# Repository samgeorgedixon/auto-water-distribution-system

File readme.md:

# Regulated Irrigation System (RIS)

**Modular, reliable and fine controlled irrigation for home to industrial greenhouses or farms, while adapting to varied temperatures and seasons to conserve water and ensure plant health.**

## Overview

Regulated Irrigation System (RIS) is modular irrigation system designed for everything from a small greenhouse to industrial farm setups. It gives you detailed control over watering routines and is able to adapt its watering output based on temperature and season. It does this while running reliably all year round unattended while conserving water.

From a phone / desktop browser you can schedule routines to water certain sets of plants at different times or intervals for durations based of current environment conditions.

#### Key Features

1. Water Plants (Water Conservation).
2. Any Environment and Scale (Greenhouse / Farm).
3. Reliable (Works for Months / Years).
4. Sustainable (Self Sufficient: Solar / Rain).
5. Relatively Affordable (< ~£100).

#### Modules

This design is made up of multiple modules which allow it to scale to any scenario with them able to sit flat on a table or be easily mounted onto a wall with keyholes.

- Command Module: Central, controlling all other modules based on the routines you have set.
- Switch modules: Add as many as needed where they interface with command to turn on certain ones of its 6 ports to power your water pumps or valves when needed.
- Valves / Pumps: Allow water to be pumped to specific sets of plants for different durations giving you full control.

#### Power

All operates off 1 battery that is charged continuously with a solar panel to ensure it can run for years in remote locations like an allotment or field.

You can then choose to power the pumps and valves by another source like mains or an external battery pack if they require more power in industrial environments.

## Small Greenhouse Scenario

To take advantage of it in this scenario you can have both sides of the greenhouse on different valves because they may get a different amount of sunlight or have different varieties of plant so one side needs more water than the other.

1. Then you can have a pump that is operated with each valve at a time taking water out of a water tank and distributing it but also have another that fills the tank every couple weeks with more water from a water butt.
2. Due to only giving the plants the water they need they will have increased yields, and it will conserve water which is important when using a water butt as when there is little rainfall it will still have leftover water.
3. As well as this due to water duration being done based of temperature, across the year plants will get more water in the summer when they need it more and little to none in the winter when they don’t need it.

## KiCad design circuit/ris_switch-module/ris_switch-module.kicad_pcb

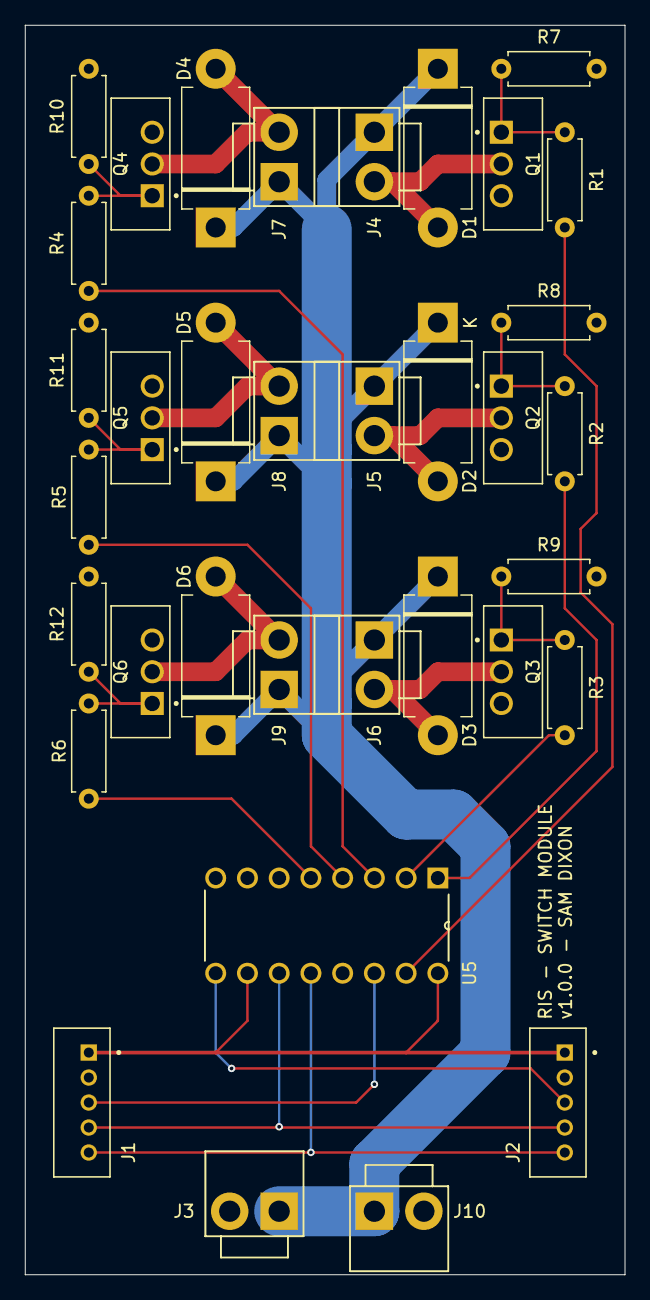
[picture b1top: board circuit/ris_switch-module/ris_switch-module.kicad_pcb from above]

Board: 2 copper layers, 48.0 x 100.0 mm, 35 parts (0 on the bottom side), 25 nets.

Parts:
D1, D2, D3, D4, D5, D6: D; D_DO-201AD_P12.70mm_Horizontal
J1, J2: JST-PH-5P-M; JST_B5B-PH-K-S
J3, J10: JST-B2PS-VH-M; B2P-VH
J4, J5, J6, J7, J8, J9: JST-PH-2P-M; B2P-VH
Q1, Q2, Q3, Q4, Q5, Q6: IRLZ44N; TO254P1054X469X1930-3
R1, R2, R3, R4, R5, R6: R-220; R_Axial_DIN0207_L6.3mm_D2.5mm_P7.62mm_Horizontal
R7, R8, R9, R10, R11, R12: R-10k; R_Axial_DIN0207_L6.3mm_D2.5mm_P7.62mm_Horizontal
U5: 74HC595N_112; DIP254P762X420-16

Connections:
GND: J1.2, J2.2, J3.2, J10.2, Q1.3, Q2.3, Q3.3, Q4.3, Q5.3, Q6.3, R7.1, R8.1, R9.1, R10.1, R11.1, R12.1, U5.8 (GND), U5.13 (~OE)
unnamed: D1.2 (A), J4.2, Q1.2
unnamed: D1.1 (K), D2.1 (K), D3.1 (K), D4.1 (K), D5.1 (K), D6.1 (K), J3.1, J4.1, J5.1, J6.1, J7.1, J8.1, J9.1, J10.1
unnamed: D2.2 (A), J5.2, Q2.2
unnamed: D3.2 (A), J6.2, Q3.2
unnamed: D4.2 (A), J7.2, Q4.2
unnamed: D5.2 (A), J8.2, Q5.2
unnamed: D6.2 (A), J9.2, Q6.2
unnamed: J1.1, J2.1, U5.10 (~MR), U5.16 (VCC)
unnamed: J1.3, U5.14 (DS)
unnamed: J1.4, J2.4, U5.11 (SH_CP)
unnamed: J1.5, J2.5, U5.12 (ST_CP)
unnamed: J2.3, U5.9 (Q7_2)
unnamed: Q1.1, R1.2, R7.2
unnamed: Q2.1, R2.2, R8.2
unnamed: Q3.1, R3.2, R9.2
unnamed: Q4.1, R4.2, R10.2
unnamed: Q5.1, R5.2, R11.2
unnamed: Q6.1, R6.2, R12.2
unnamed: R1.1, U5.15 (Q0)
unnamed: R2.1, U5.1 (Q1)
unnamed: R3.1, U5.2 (Q2)
unnamed: R4.1, U5.3 (Q3)
unnamed: R5.1, U5.4 (Q4)
unnamed: R6.1, U5.5 (Q5)

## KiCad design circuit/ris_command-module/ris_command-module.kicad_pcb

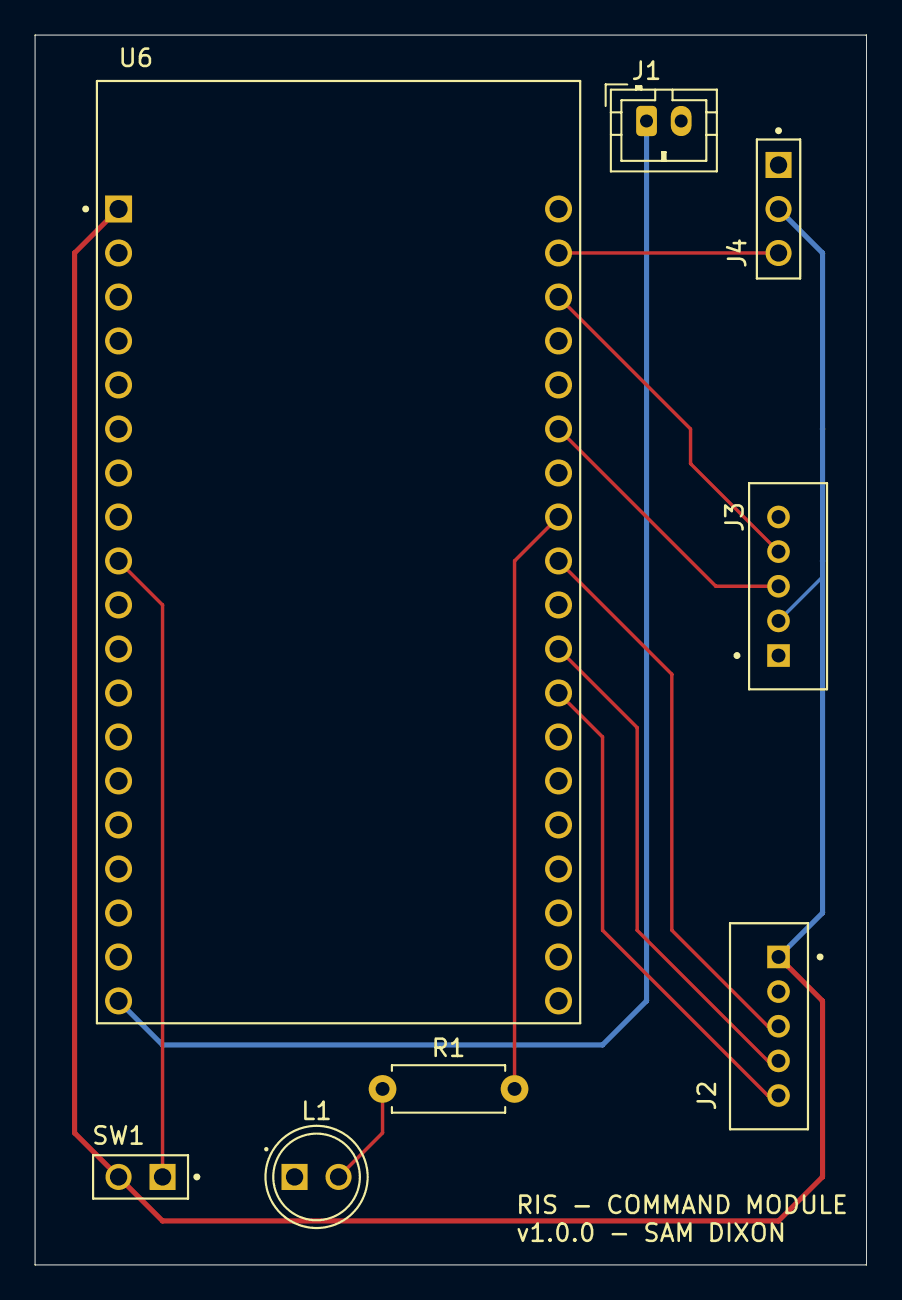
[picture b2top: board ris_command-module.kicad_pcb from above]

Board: 2 copper layers, 48.0 x 71.0 mm, 8 parts (0 on the bottom side), 12 nets.

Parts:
J1: JST-PH-2P-M_5V; JST_PH_B2B-PH-K_1x02_P2.00mm_Vertical
J2: JST-PH-5P-M; JST_B5B-PH-K-S
J3: JST-PH-5P-M_ZS042; JST_B5B-PH-K-S
J4: Header-3P-F_DHT22; HARWIN_M20-7820346
L1: WP7113ID; LED_WP7113ID
R1: R-220; R_Axial_DIN0207_L6.3mm_D2.5mm_P7.62mm_Horizontal
SW1: SW_DIP_x01; HARWIN_M20-7820242
U6: ESP32-DEVKITC-32D; MODULE_ESP32-DEVKITC-32D

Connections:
+3.3V: J2.1, J3.2, J4.2, SW1.2, U6.J2-1 (3V3)
+5V: J1.1, U6.J2-19 (EXT_5V)
GND: J1.2, J2.2, J3.1, J4.1, L1.C, U6.J3-1 (GND3)
unnamed: J2.3, U6.J3-9 (IO18)
unnamed: J2.4, U6.J3-11 (IO17)
unnamed: J2.5, U6.J3-12 (IO16)
unnamed: J3.3, U6.J3-6 (IO21)
unnamed: J3.4, U6.J3-3 (IO22)
unnamed: J4.3, U6.J3-2 (IO23)
unnamed: L1.A, R1.1
unnamed: R1.2, U6.J3-8 (IO19)
unnamed: SW1.1, U6.J2-9 (IO25)

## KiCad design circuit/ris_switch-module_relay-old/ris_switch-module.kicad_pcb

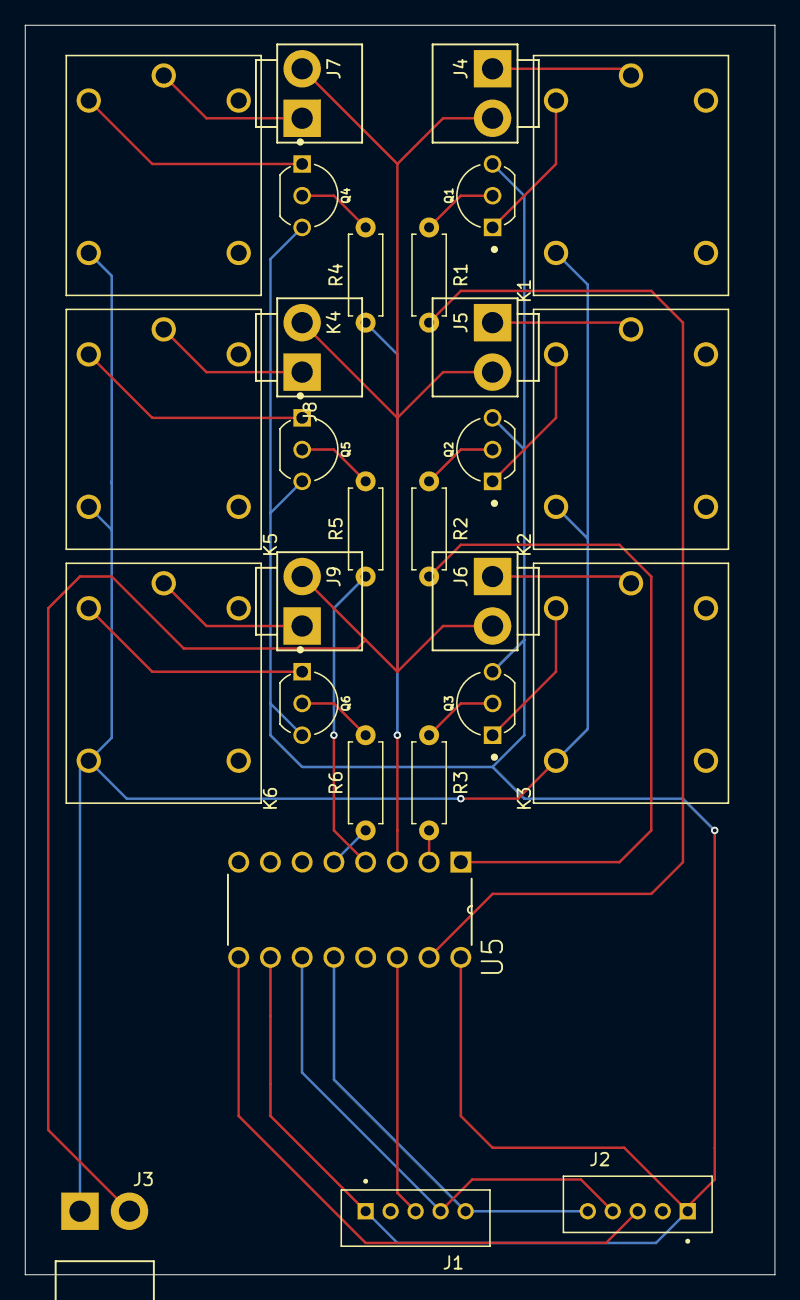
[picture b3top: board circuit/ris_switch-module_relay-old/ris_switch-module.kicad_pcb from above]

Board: 2 copper layers, 60.0 x 100.0 mm, 28 parts (0 on the bottom side), 32 nets.

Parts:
J1, J2: JST-PH-5P-M; JST_B5B-PH-K-S
J3: JST-B2PS-VH-M; B2PS-VH
J4, J5, J6, J7, J8, J9: JST-PH-2P-M; B2P-VH
K1, K2, K3, K4, K5, K6: SRD-03VDC-SL-C; RELAY_SRD-03VDC-SL-C
Q1, Q2, Q3, Q4, Q5, Q6: BC337-40; TO92254P520H877-3
R1, R2, R3, R4, R5, R6: R-470; R_Axial_DIN0207_L6.3mm_D2.5mm_P7.62mm_Horizontal
U5: 74HC595N_112; DIP254P762X420-16

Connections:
unnamed: J1.1, J2.1, Q1.3 (C), Q2.3 (C), Q3.3 (C), Q4.3 (C), Q5.3 (C), Q6.3 (C), U5.10 (~MR), U5.16 (VCC)
unnamed: J1.2, J2.2, K1.COIL1, K2.COIL1, K3.COIL1, K4.COIL1, K5.COIL1, K6.COIL1, U5.8 (GND), U5.13 (~OE)
unnamed: J1.3, U5.14 (DS)
unnamed: J1.4, J2.4, U5.11 (SH_CP)
unnamed: J1.5, J2.5, U5.12 (ST_CP)
unnamed: J2.3, U5.9 (Q7_2)
unnamed: J3.1, K1.NO, K2.NO, K3.NO, K4.NO, K5.NO, K6.NO
unnamed: J3.2, J4.2, J5.2, J6.2, J7.2, J8.2, J9.2
unnamed: J4.1, K1.COM
unnamed: J5.1, K2.COM
unnamed: J6.1, K3.COM
unnamed: J7.1, K4.COM
unnamed: J8.1, K5.COM
unnamed: J9.1, K6.COM
unnamed: Q1.2 (B), R1.2
unnamed: K1.COIL2, Q1.1 (E)
unnamed: Q2.2 (B), R2.2
unnamed: K2.COIL2, Q2.1 (E)
unnamed: Q3.2 (B), R3.2
unnamed: K3.COIL2, Q3.1 (E)
unnamed: Q4.2 (B), R4.2
unnamed: K4.COIL2, Q4.1 (E)
unnamed: Q5.2 (B), R5.2
unnamed: K5.COIL2, Q5.1 (E)
unnamed: Q6.2 (B), R6.2
unnamed: K6.COIL2, Q6.1 (E)
unnamed: R1.1, U5.15 (Q0)
unnamed: R2.1, U5.1 (Q1)
unnamed: R3.1, U5.2 (Q2)
unnamed: R4.1, U5.3 (Q3)
unnamed: R5.1, U5.4 (Q4)
unnamed: R6.1, U5.5 (Q5)

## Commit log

2025-07-30 Added Git
2025-07-31 Added Flow System Diagram
2025-07-31 Added Circuit and Model CAD
2025-08-04 Added Basic Model Blocks
2025-09-07 Added Component Orders Spreadsheet
2025-09-07 Added Command and Switch Modules
2025-11-08 Updated README with Plan & Reorganised Folders
2025-11-08 Added Command Module Circuit
2025-11-08 Updated Circuit
2025-11-09 Updated Model
2025-11-09 Added Switches and LED to Circuit
2025-11-12 Updated Component Orders with Exact Electronic Components
2025-11-15 Updated Model with Perfboard
2025-11-18 Added Program with Components
2025-11-23 Updated Program with Network and Flow
2025-11-23 Changed Name to Regulated Irrigation System (RIS)
2025-12-03 Updated Program with Routines & Time & Saving
2025-12-14 Added Command & Switch PCBs
2025-12-19 Updated Program with Pump / Valve Port Selections
2025-12-20 Updated Program with HTML Refactor + Pin Skips
2025-12-22 Updated Program with Current / Power Limits
2025-12-27 Fitted Electronic Components into Model
2025-12-30 Updated Program with Input Limits & Time & Power Saving
2025-12-31 Updated Circuit with Side Outputs & Mosfets
2026-01-02 Updated Model with Connectors / Slots
2026-01-02 Updated Model with Time & Temperature Enclosure Parts
2026-01-03 Updated Model with Keyhole Mounting to Slot Module
2026-01-03 Updated Model with Solar Charger Connector
2026-01-03 Updated Model with Valve Module
2026-01-03 Added Design & Presentation Documents
2026-01-04 Fixed Circuit by DRC
2026-01-04 Updated Component Orders
2026-01-17 Exported Circuits to Gerber files
2026-01-17 Updated Order List
2026-01-18 Updated Order List with Separated Components
2026-02-13 Updated Model Tolerances
2026-02-22 Fixed Model Tolerances
2026-02-22 Fixed Program with Routine Starting & Switch Logic
2026-03-01 Fixed Program with Routines Timing
2026-03-12 Refactored Project Structure
2026-03-14 Updated License with Hardware & Software Licenses
2026-03-14 Removed .code-workspace
2026-03-14 Release: v0.1.0
    commit 395d54a6aa0ec5e2283e6a57e1ed26b426e7688f
    Author: Sam Dixon <samgeorgedixon@gmail.com>
    Date: Sat Mar 14 11:14:19 2026 +0000
    Removed .code-workspace
    commit e84a8b03ed0aea64cf1571eb71c593b8f5143728
    Author: Sam Dixon <samgeorgedixon@gmail.com>
